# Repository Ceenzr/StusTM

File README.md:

# StusTM
Scanning Tunneling Microscope - StusTM

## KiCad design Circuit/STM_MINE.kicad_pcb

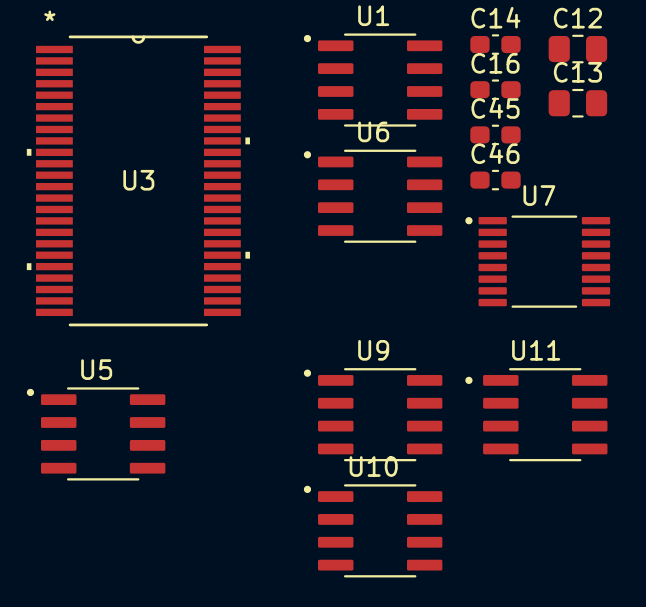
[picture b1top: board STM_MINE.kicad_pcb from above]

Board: 2 copper layers, 14 parts (0 on the bottom side), 13 nets, no tracks yet.

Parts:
C12, C13: 10uF; C_0805_2012Metric_Pad1.18x1.45mm_HandSolder
C14, C45, C46: 1uF; C_0603_1608Metric_Pad1.08x0.95mm_HandSolder
C16: 10pF; C_0603_1608Metric_Pad1.08x0.95mm_HandSolder
U1: REF5040AID; SOIC127P599X175-8N
U3: DAC7734EB; DL48
U5: OPA627AU; SOIC127P599X175-8N
U6: OPA1612AIDR; SOIC127P599X175-8N
U7: ADS8681IPWR; SOP65P640X120-16N
U9, U10: OPA2227UAG4; SOIC127P599X175-8N
U11: OPA227U; SOIC127P599X175-8N

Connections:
+3.3V: C46.1, U7.16 (DVDD)
+5V: C45.1, U1.2 (VIN), U7.2 (AVDD)
+15V: U5.7 (+VS), U6.8 (V+), U9.8 (V+), U10.8 (V+), U11.7 (V+)
-15V: U5.4 (-VS), U6.4 (V-), U9.4 (V-), U10.4 (V-), U11.4 (V-)
AGND: C12.1, C13.1, C14.1, C45.2, U1.4 (GND), U5.3 (+IN), U7.3 (AGND), U7.5 (REFGND), U11.3 (+IN)
DGND: C46.2, U7.1 (DGND)
GND: U9.3 (+INA), U10.3 (+INA)
unnamed: C13.2, C14.2
unnamed: U6.1 (OUT_A), U6.2 (-IN_A)
unnamed: U6.6 (-IN_B), U6.7 (OUT_B)
unnamed: C16.1, U7.8 (AIN_GND)
unnamed: C16.2, U7.7 (AIN_P)
unnamed: U11.1 (TRIM), U11.8 (TRIM)

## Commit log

2025-07-14 Create KiCAD
2025-07-14 Create
2025-07-15 Update documentation.md
    DAC decisions
2025-07-16 Update documentation.md
    DAC was selected (though still searching for potential better alternative)
